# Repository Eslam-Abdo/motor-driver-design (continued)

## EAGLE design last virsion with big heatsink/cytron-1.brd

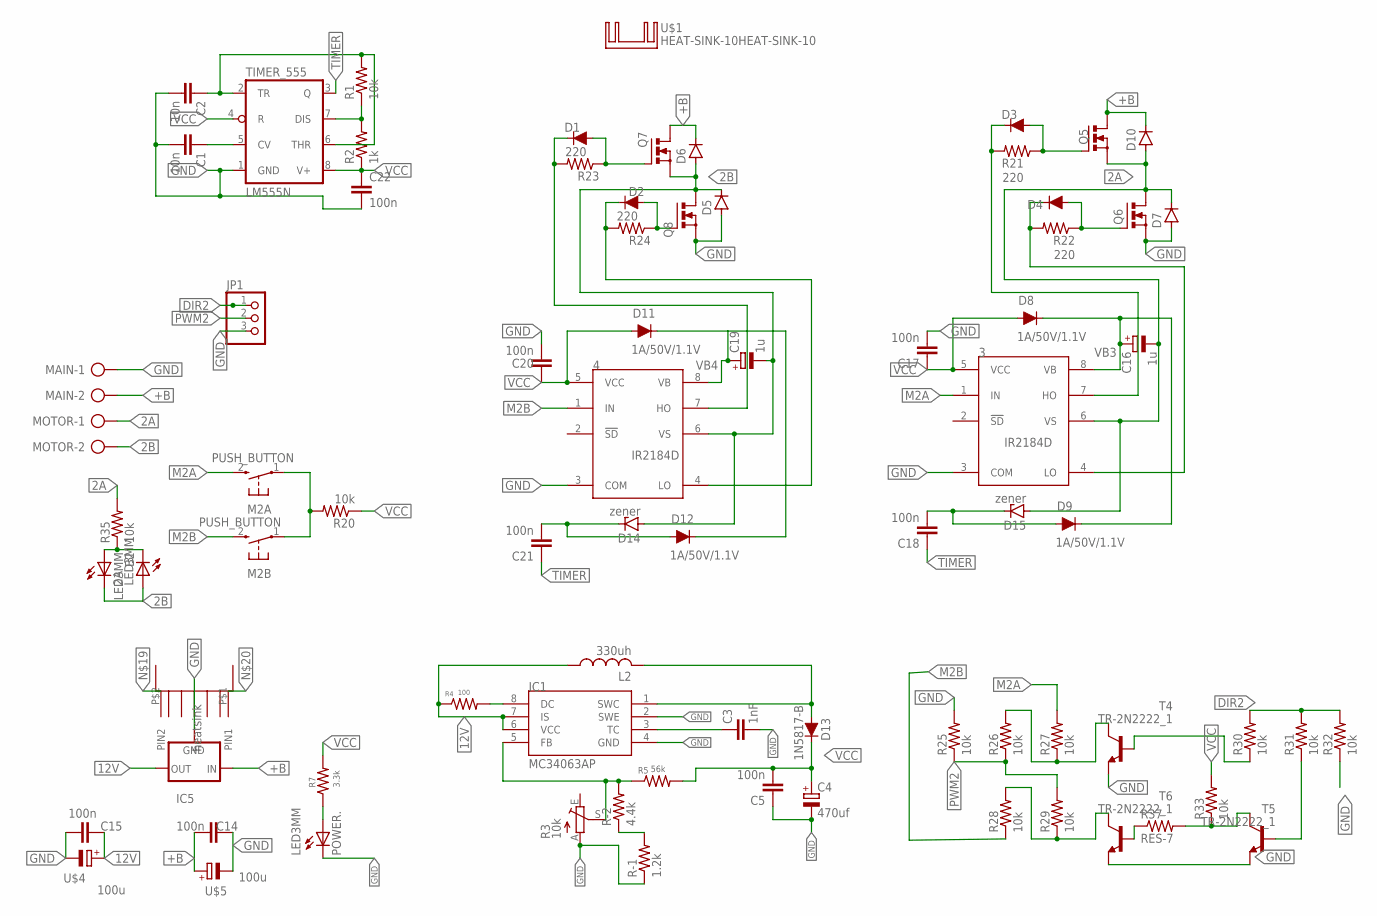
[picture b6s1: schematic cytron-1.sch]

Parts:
2A: LED3MM
3, 4: IR2184D; DIL08
B2: LED3MM
C1, C2: 10n; C025-025X050
C3: 1nF; C025-025X050
C4: 470uf; E3,5-8
C5, C14, C15, C17, C18, C20, C21, C22: 100n; C025-025X050
C16, C19: 1u; E5-5
D1, D2, D3, D4, D8, D9, D11, D12: 1A/50V/1.1V; DIODE-1N4001
D5, D6, D7, D10: BY396; DO201-15
D13: 1N5817-B; DIODE-1N4001
D14, D15: zener; SOD81
IC1: MC34063AP; DIL08
IC5: 78XXS
JP1: PINHD-3_DATA; 1X03_DATA
L2: 330uh; PIS2816
M2A, M2B: PUSH_BUTTON; B3F-10XX
MAIN: ROSTA.POWER; W239-302
MOTOR: ROSTA.POWER; W239-302
POWER.: LED3MM
Q5, Q6, Q7, Q8: MOSFET_NTO220BV; TO220BV
R1, R20, R25, R26, R27, R28, R29, R30, R31, R32, R33, R35: 10k; 0204/7
R2: 1k; 0204/7
R3: 10k; CA6V
R4: 100; 0204/7
R5: 56k; 0204/7
R7: 3.3k; 0204/7
R21, R22, R23, R24: 220; 0204/7
R37: RES-7; 0204/7
R-1: 1.2k; 0204/7
R-2: 4.4k; 0204/7
T4, T5, T6: TR-2N2222_1; TO92-EBC
TIMER_555: LM555N; DIL08
U$1: HEAT-SINK-10HEAT-SINK-10; HS10
U$3: HEAT-SINK; HEAT_SINK
U$4, U$5: 100u; E3,5-8

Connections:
2A: 3.6 (VS), C16.-, D7.C, D10.A, D15.A, MOTOR.1, Q5.S, Q6.D, R35.2
2B: 2A.K (C), 4.6 (VS), B2.A, C19.-, D5.C, D6.A, D14.A, MOTOR.2, Q7.S, Q8.D
12V: C15.2, IC1.6 (VCC), IC1.7 (IS), IC5.OUT, L2.1, R4.1, U$4.+
+B: C14.1, D6.C, D10.C, IC5.IN, MAIN.2, Q5.D, Q7.D, U$5.+
DIR2: JP1.1, R30.2, R31.2, R32.2
GND: 3.3 (COM), 4.3 (COM), C1.2, C2.2, C3.2, C4.-, C5.1, C14.2, C15.1, C17.2, C20.2, C22.2, D5.A, D7.A, IC1.2 (SWE), IC1.4 (GND), IC5.GND, JP1.3, MAIN.1, POWER..K (C), Q6.S, Q8.S, R3.A, R25.2, R32.1, R-1.1, T4.E, T5.E, T6.E, TIMER_555.1 (GND), U$4.-, U$5.-
M2A: 3.1 (IN), M2A.2 (S), R27.2
M2B: 4.1 (IN), M2B.2 (S), R28.1
unnamed: C1.1, TIMER_555.5 (CV)
unnamed: R1.1, R2.2, TIMER_555.7 (DIS)
unnamed: C2.1, R1.2, TIMER_555.2 (TR), TIMER_555.6 (THR)
unnamed: D4.A, Q6.G, R22.1
unnamed: 3.4 (LO), D4.C, R22.2
unnamed: M2A.1, M2B.1, R20.2
unnamed: R37.1, T6.B
unnamed: C3.1, IC1.3 (TC)
unnamed: D13.A, IC1.1 (SWC), L2.2
unnamed: 4.7 (HO), D1.C, R23.2
unnamed: IC1.5 (FB), R3.S, R5.1, R-2.2
unnamed: 4.4 (LO), D2.C, R24.2
unnamed: IC1.8 (DC), R4.2
unnamed: POWER..A, R7.1
unnamed: R-1.2, R-2.1
unnamed: D3.A, Q5.G, R21.1
unnamed: 3.7 (HO), D3.C, R21.2
unnamed: C18.2, D9.A, D15.C
unnamed: D2.A, Q8.G, R24.1
unnamed: D1.A, Q7.G, R23.1
unnamed: C21.2, D12.A, D14.C
unnamed: R28.2, R29.1, T6.C
unnamed: R26.2, R27.1, T4.C
unnamed: R30.1, T4.B
unnamed: R33.1, R37.2, T5.C
unnamed: R31.1, T5.B
unnamed: 2A.A, B2.K (C), R35.1
PWM2: JP1.2, R25.1, R26.1, R29.2
TIMER: C18.1, C21.1, TIMER_555.3 (Q)
VB3: 3.8 (VB), C16.+, D8.C, D9.C
VB4: 4.8 (VB), C19.+, D11.C, D12.C
VCC: 3.5 (VCC), 4.5 (VCC), C4.+, C5.2, C17.1, C20.1, C22.1, D8.A, D11.A, D13.C, R2.1, R5.2, R7.2, R20.1, R33.2, TIMER_555.4 (R), TIMER_555.8 (V+)

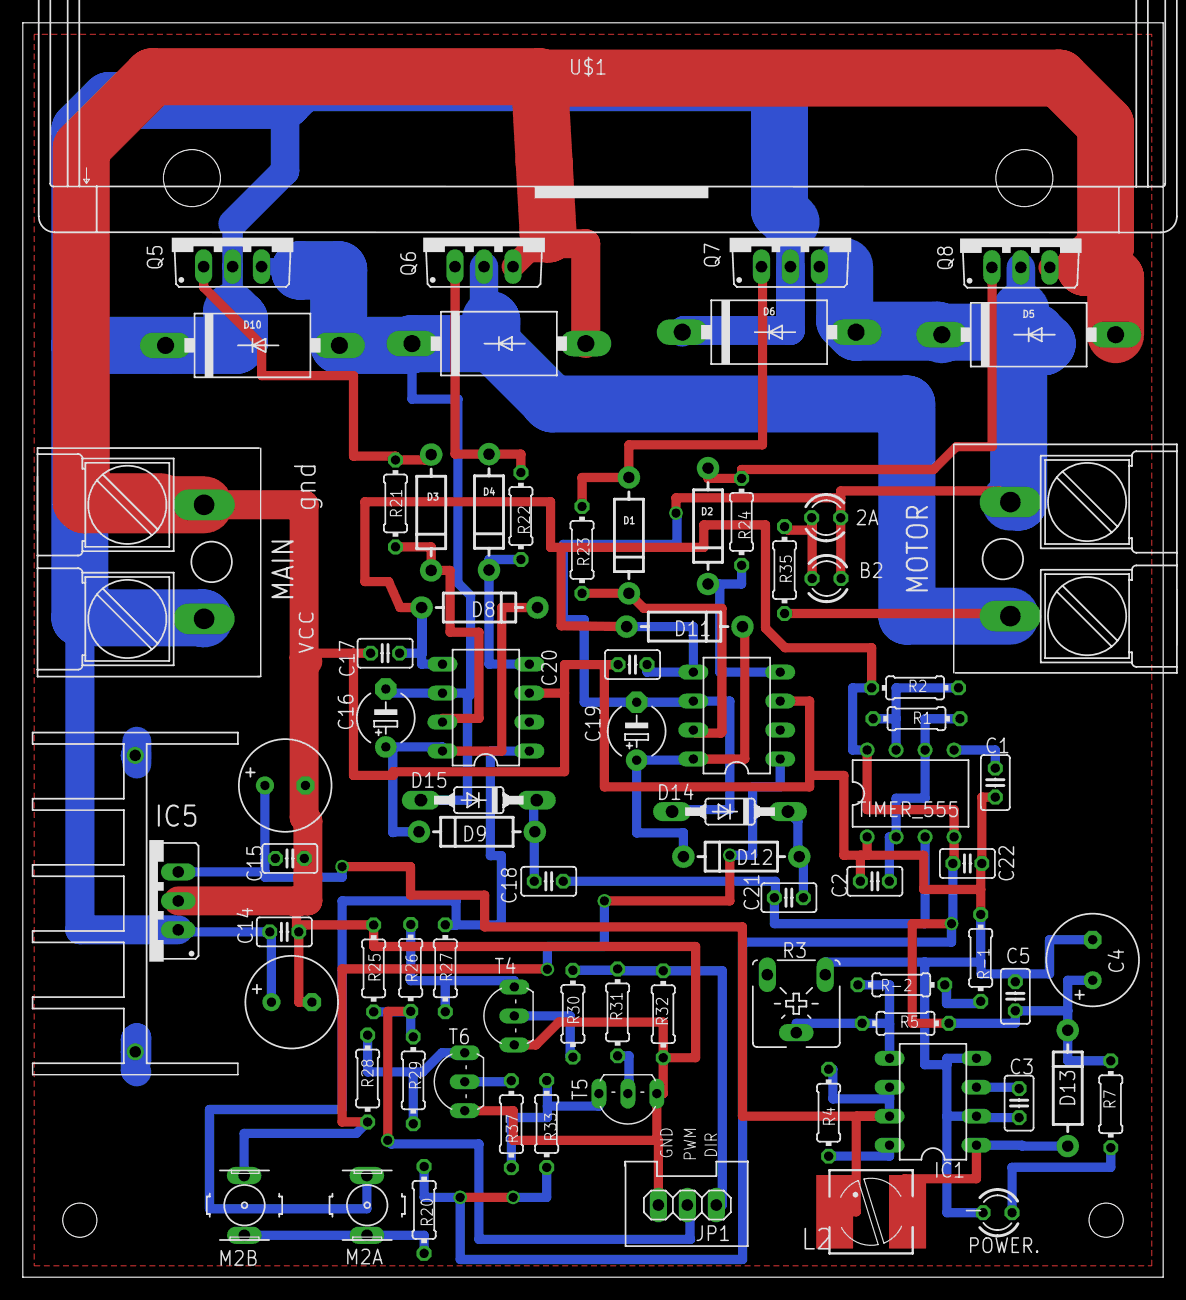
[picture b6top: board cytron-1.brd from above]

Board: 2 copper layers, 100.0 x 110.0 mm, 78 parts (0 on the bottom side), 40 nets.

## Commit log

2023-04-15 add files
